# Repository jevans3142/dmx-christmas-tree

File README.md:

# dmx-christmas-tree
DMX-controlled 3D RGB christmas tree - based on PiHut tree for RPi, running on an esp32

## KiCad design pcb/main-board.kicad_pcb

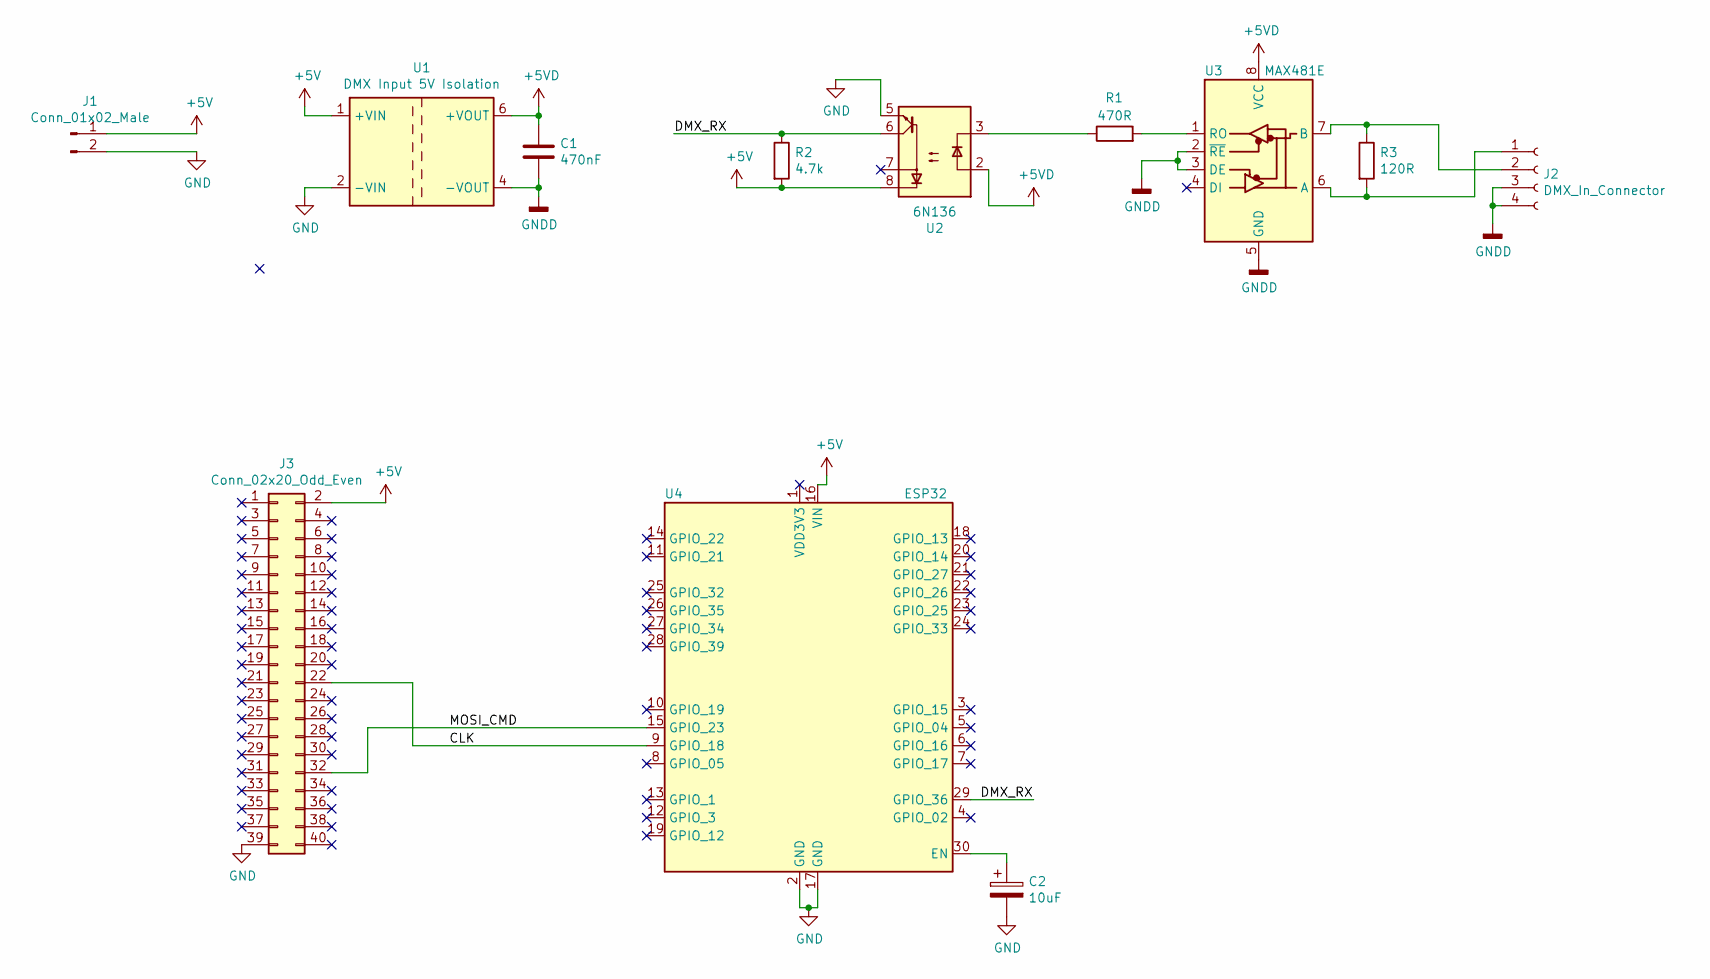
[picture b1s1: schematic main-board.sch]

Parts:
C1: 470nF; C_Rect_L7.2mm_W5.5mm_P5.00mm_FKS2_FKP2_MKS2_MKP2
C2: 10uF; CP_Radial_D6.3mm_P2.50mm
J1: Conn_01x02_Male; PinHeader_1x02_P2.54mm_Vertical
J2: DMX_In_Connector; Krone_4_Way_terminal
J3: Conn_02x20_Odd_Even; PinHeader_2x20_P2.54mm_Vertical
R1: 470R; R_Axial_DIN0207_L6.3mm_D2.5mm_P10.16mm_Horizontal
R2: 4.7k; R_Axial_DIN0207_L6.3mm_D2.5mm_P10.16mm_Horizontal
R3: 120R; R_Axial_DIN0207_L6.3mm_D2.5mm_P10.16mm_Horizontal
U1: DMX Input 5V Isolation; Traco_TMA_DCDCsingle
U2: 6N136; DIP-8_W7.62mm_Socket
U3: MAX481E; DIP-8_W7.62mm_Socket
U4: ESP32; ESP32_DOIT30

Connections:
+5V: J1.1, J3.2, R2.2, U1.1 (+VIN), U2.8, U4.16 (VIN)
+5VD: C1.1, U1.6 (+VOUT), U2.2, U3.8 (VCC)
/CLK: J3.22, U4.9 (GPIO_18)
/DMX_RX: R2.1, U2.6, U4.29 (GPIO_36)
/MOSI_CMD: J3.32, U4.15 (GPIO_23)
GND: C2.2, J1.2, J3.39, U1.2 (-VIN), U2.5, U4.2 (GND), U4.17 (GND)
GNDD: C1.2, J2.3, J2.4, U1.4 (-VOUT), U3.2 (~RE), U3.3 (DE), U3.5 (GND)
unnamed: C2.1, U4.30 (EN)
unnamed: J2.1, R3.2, U3.6 (A)
unnamed: J2.2, R3.1, U3.7 (B)
unnamed: R1.1, U2.3
unnamed: R1.2, U3.1 (RO)

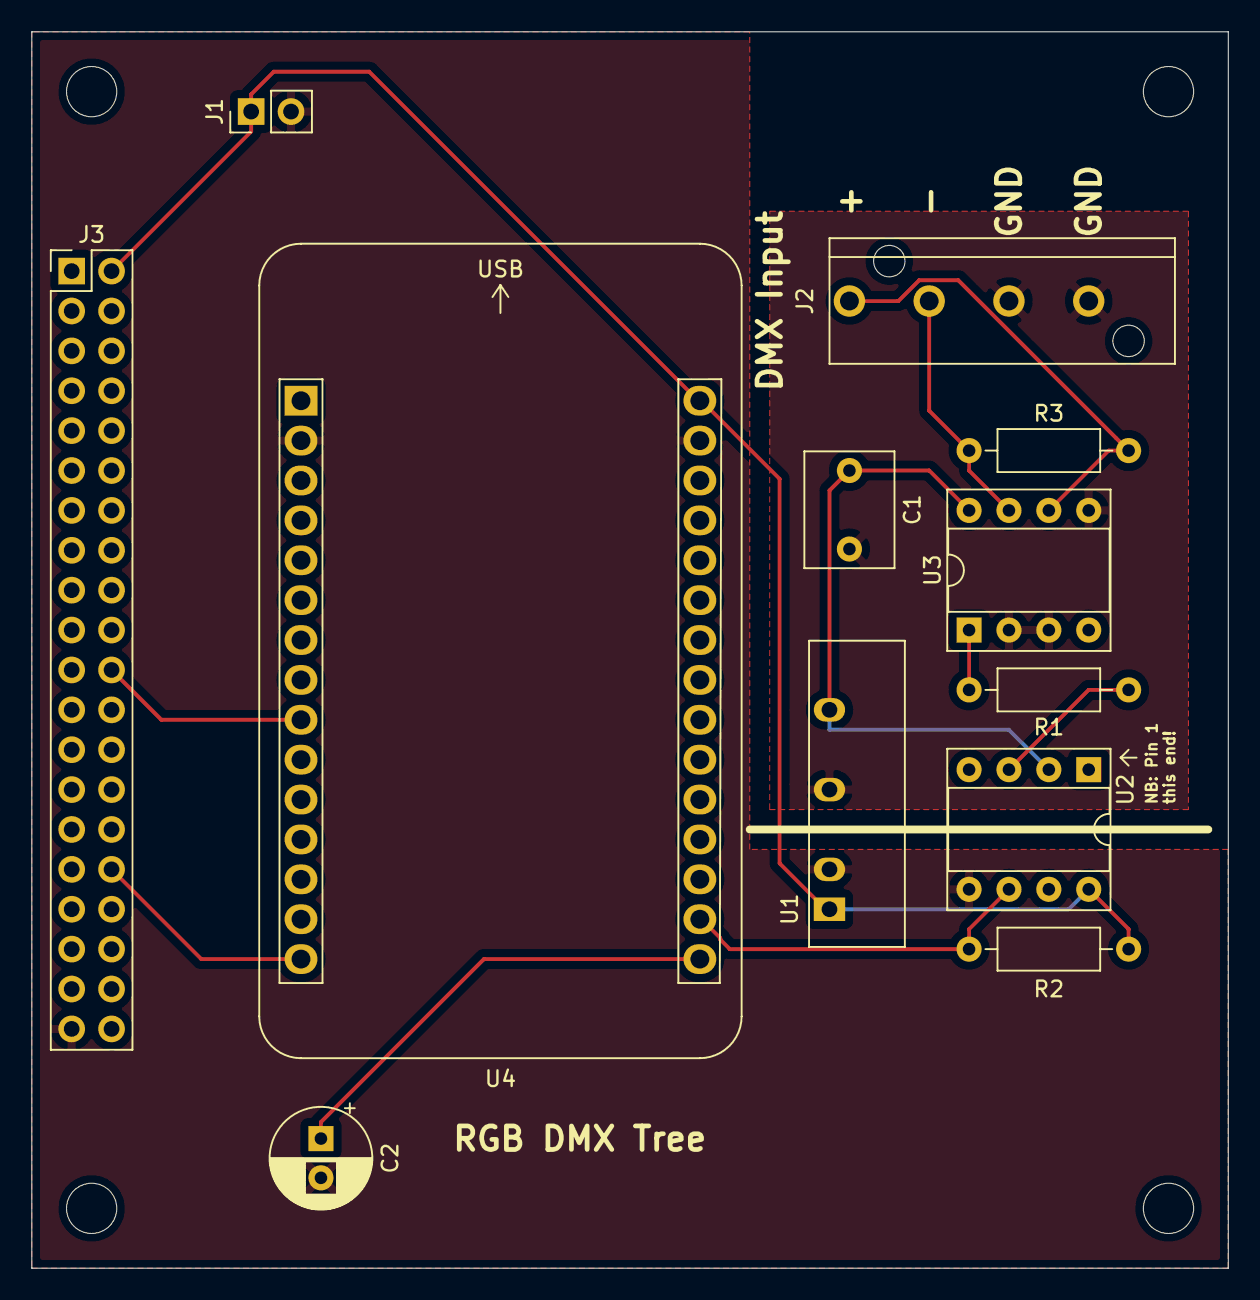
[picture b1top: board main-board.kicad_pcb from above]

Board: 2 copper layers, 76.2 x 78.7 mm, 12 parts (0 on the bottom side), 12 nets.

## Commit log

2020-11-28 Add gitignore/attributes files
    Correctly ignore build files and classify h files
2020-11-29 Blank code files
    Compiles under esp-idf 4.3 - boilerplate
2020-11-29 PCB first draft
2020-11-29 Working test code
    This works with the LEDs and displays an RGB pattern - no motion or DMX interaction yet
2020-11-29 Save LED datasheet
    Datasheet for the LEDs used on the christmas tree from PiHut
